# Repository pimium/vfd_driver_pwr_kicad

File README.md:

# VFD_Driver_FUTABA_7-LT-44Z
Driver for the VFD-Display from [Pollin](https://www.pollin.de/p/vakuum-fluoreszenzdisplay-futaba-7-lt-44z-4-digit-121538).

The driver uses:
- 74hc595 shift register
- TBD62783 high side driver
- NPN and PNP transistors as high side driver.

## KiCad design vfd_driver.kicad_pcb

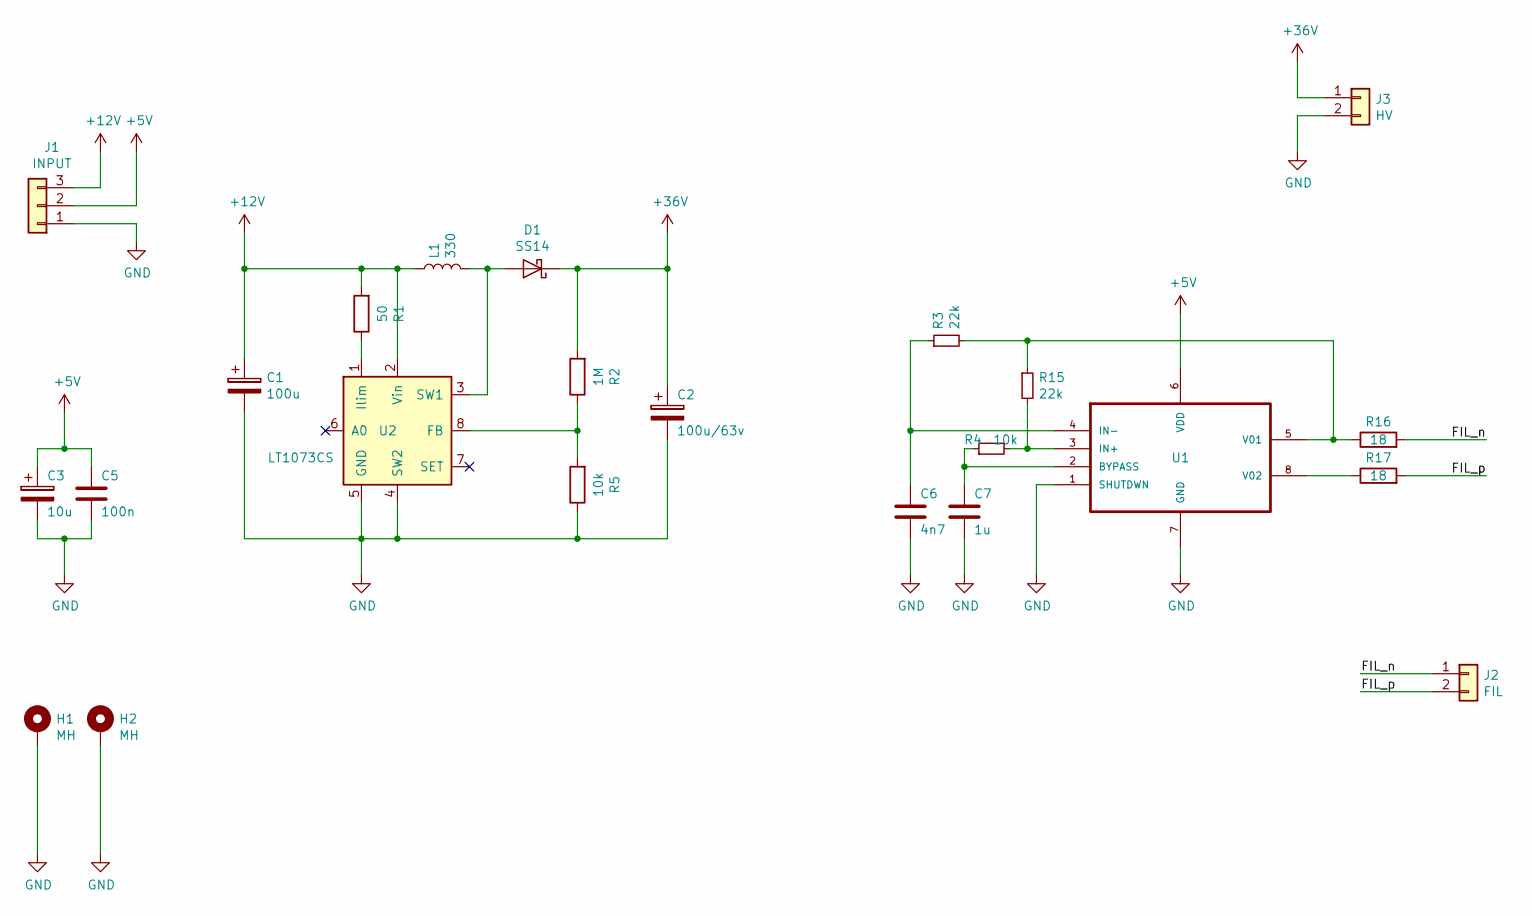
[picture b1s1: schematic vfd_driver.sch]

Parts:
C1: 100u; CP_EIA-7343-15_Kemet-W_Pad2.25x2.55mm_HandSolder
C2: 100u/63v; CP_Radial_D8.0mm_P5.00mm
C3: 10u; CP_Radial_D8.0mm_P3.80mm
C5: 100n; C_0805_2012Metric_Pad1.15x1.40mm_HandSolder
C6: 4n7; C_0805_2012Metric_Pad1.15x1.40mm_HandSolder
C7: 1u; C_Rect_L7.0mm_W2.0mm_P5.00mm
D1: SS14; D_SMA_Handsoldering
H1, H2: MH; MountingHole_3.2mm_M3_DIN965_Pad
J1: INPUT; PinHeader_1x03_P2.54mm_Vertical
J2: FIL; PinHeader_1x02_P2.54mm_Vertical
J3: HV; PinHeader_1x02_P2.54mm_Vertical
L1: 330; Choke_CD75
R1: 50; R_0805_2012Metric_Pad1.15x1.40mm_HandSolder
R2: 1M; R_0805_2012Metric_Pad1.15x1.40mm_HandSolder
R3, R15: 22k; R_0805_2012Metric_Pad1.15x1.40mm_HandSolder
R4, R5: 10k; R_0805_2012Metric_Pad1.15x1.40mm_HandSolder
R16, R17: 18; R_1206_3216Metric_Pad1.42x1.75mm_HandSolder
U1: LM4871; SOIC-8_3.9x4.9mm_P1.27mm
U2: LT1073CS; SOIC-8_3.9x4.9mm_P1.27mm

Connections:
+5V: C3.1, C5.1, J1.2, U1.6 (VDD)
+12V: C1.1, J1.3, L1.1, R1.2, U2.2 (Vin)
+36V: C2.1, D1.1 (K), J3.1, R2.2
/FIL_n: J2.1, R16.2
/FIL_p: J2.2, R17.2
GND: C1.2, C2.2, C3.2, C5.2, C6.2, C7.2, H1.1, H2.1, J1.1, J3.2, R5.1, U1.1 (SHUTDWN), U1.7 (GND), U2.4 (SW2), U2.5 (GND)
unnamed: C6.1, R3.1, U1.4 (IN-)
unnamed: C7.1, R4.1, U1.2 (BYPASS)
unnamed: D1.2 (A), L1.2, U2.3 (SW1)
unnamed: R1.1, U2.1 (Ilim)
unnamed: R2.1, R5.2, U2.8 (FB)
unnamed: R3.2, R15.1, R16.1, U1.5 (V01)
unnamed: R4.2, R15.2, U1.3 (IN+)
unnamed: R17.1, U1.8 (V02)

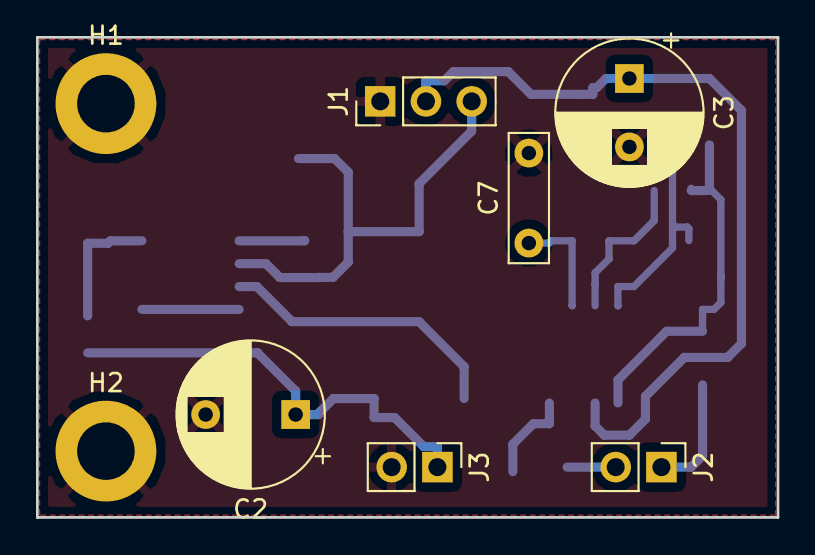
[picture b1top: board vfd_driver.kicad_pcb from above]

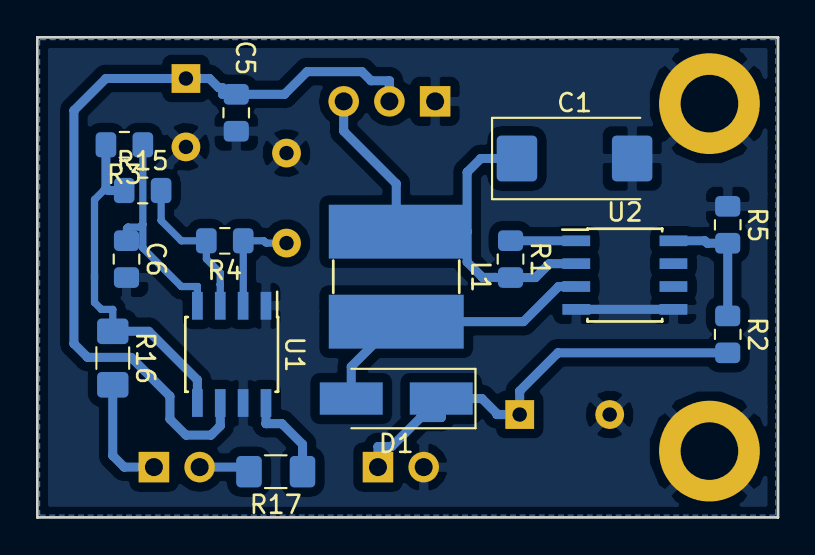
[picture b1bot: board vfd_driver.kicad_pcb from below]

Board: 2 copper layers, 41.1 x 26.7 mm, 23 parts (15 on the bottom side), 14 nets.

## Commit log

2018-12-07 My first commit
2018-12-07 schematic is done
2018-12-09 add the datasheet of the vfd display
2018-12-15 working on layout
2018-12-15 zwischenschritt
2019-02-20 remove the ISP connector
2019-02-20 Remove the attiny13 and using the n555 fo high voltage generation.
2019-02-20 Add lm4871
2019-03-10 pwr and logic separed
2019-04-04 Power and logic are separated and working well.
2019-04-11 Add a 4th shift register and suppress the grad-pin input
2019-04-13 add a protecting diode to the power input.
2019-04-13 Separated input for the step up driver so ca be supply with 12V.
2019-04-13 before adding lt1073
2019-04-13 add marks that helps, when the board is drilled.
2019-04-27 rescue parts
